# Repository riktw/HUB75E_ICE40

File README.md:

# HUB75E_ICE40
SpinalHDL code to drive a 64*64 pixel HUB75E module with an ICE40

This code is used to drive a HUB75E dislay, fast enough to display animated gifs:

This project uses SpinalHDL, see installation notes here: https://spinalhdl.github.io/SpinalDoc-RTD/SpinalHDL/Getting%20Started/index.html

To build, yosys and nextpnr are used, see installation notes here: http://www.clifford.at/icestorm/

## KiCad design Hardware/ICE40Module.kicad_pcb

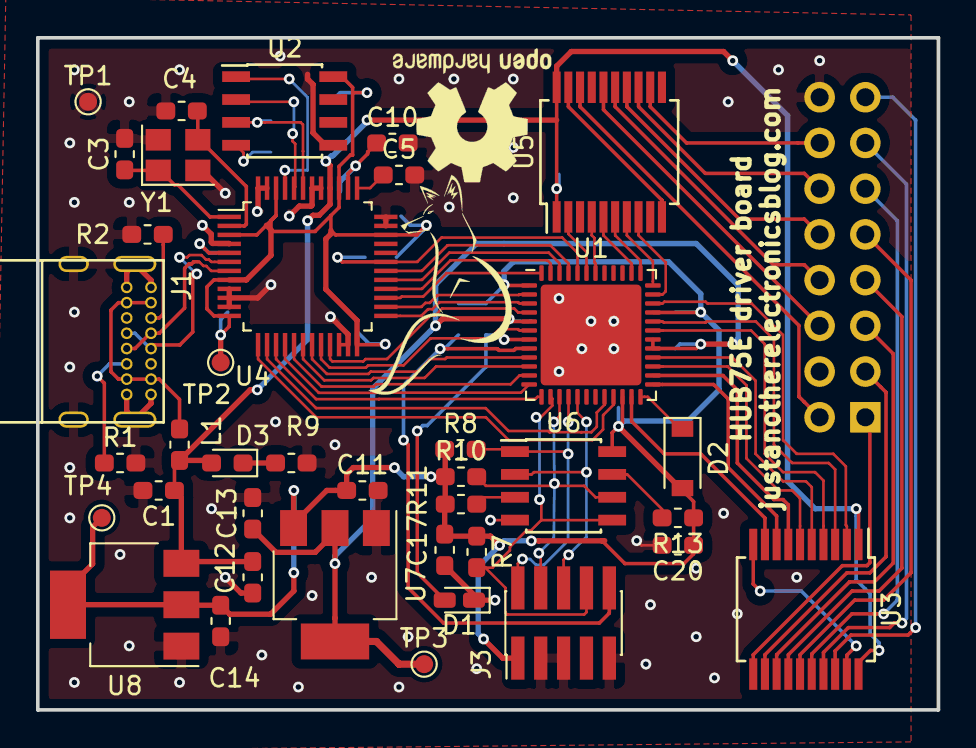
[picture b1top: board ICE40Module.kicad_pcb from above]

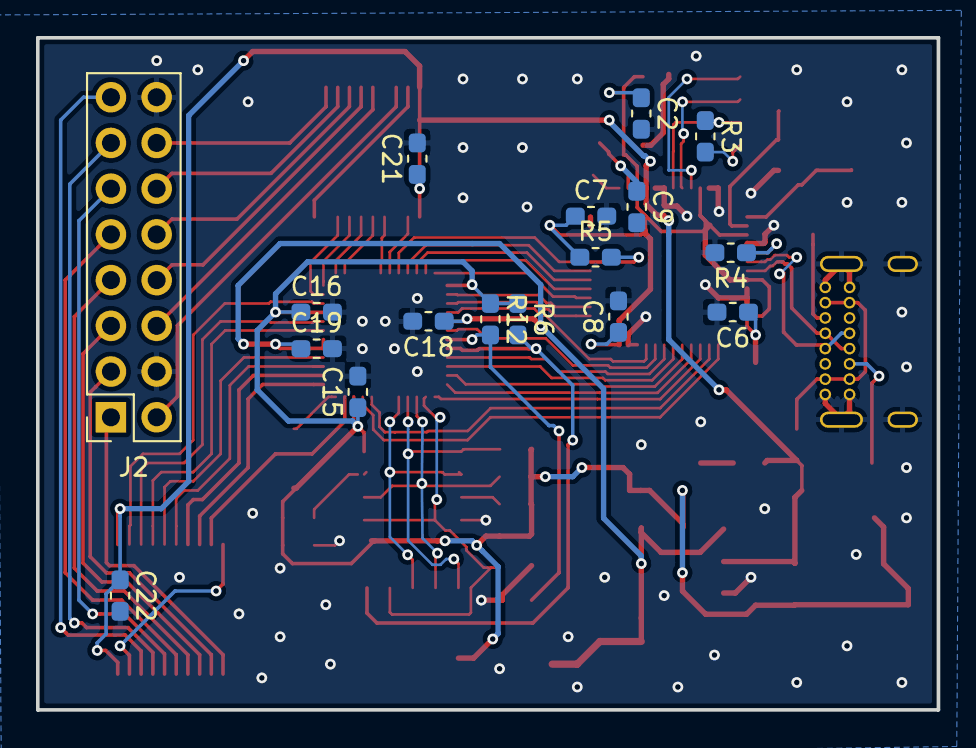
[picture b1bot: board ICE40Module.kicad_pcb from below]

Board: 2 copper layers, 50.0 x 37.3 mm, 55 parts (17 on the bottom side), 75 nets.

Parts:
C1, C8, C10, C18: 1u; C_0603_1608Metric_Pad1.05x0.95mm_HandSolder
C2, C5, C6, C7, C9, C11, C12, C13, C14, C15, C16, C17, C19, C20, C21, C22: 100n; C_0603_1608Metric_Pad1.05x0.95mm_HandSolder
C3, C4: 18p; C_0603_1608Metric_Pad1.05x0.95mm_HandSolder
D1: LED; LED_0603_1608Metric_Castellated
D2: MBR0520; D_SOD-123
D3: LED; LED_0603_1608Metric_Pad1.05x0.95mm_HandSolder
J1: USB_C_Recept_16Pin
J2: Conn_02x08_Odd_Even; PinSocket_2x08_P2.54mm_Vertical
J3: Conn_ARM_JTAG_SWD_10; PinHeader_2x05_P1.27mm_Vertical_SMD
L1: 22R; L_0603_1608Metric_Pad1.05x0.95mm_HandSolder
R1, R2, R5: 5.1K; R_0603_1608Metric_Pad1.05x0.95mm_HandSolder
R3, R12: 2.2K; R_0603_1608Metric_Pad1.05x0.95mm_HandSolder
R4: 12K; R_0603_1608Metric_Pad1.05x0.95mm_HandSolder
R6, R7, R8, R10, R11, R13: 10K; R_0603_1608Metric_Pad1.05x0.95mm_HandSolder
R9: 680R; R_0603_1608Metric_Pad1.05x0.95mm_HandSolder
TP1, TP2, TP3, TP4: TP; TestPoint_Pad_D1.0mm
U1: ICE40UP5K-SG48ITR; QFN-48-1EP_7x7mm_P0.5mm_EP5.6x5.6mm
U2: 93LCxxB; SOIC-8_3.9x4.9mm_P1.27mm
U3, U5: 74HC245; SSOP-20_5.3x7.2mm_P0.65mm
U4: FT232H; LQFP-48_7x7mm_P0.5mm
U6: AT25SF081-SSHD-X; SOIC-8_3.9x4.9mm_P1.27mm
U7: AZ1117-1.2; SOT-223-3_TabPin2
U8: AP1117-33; SOT-223-3_TabPin2
Y1: 12Mhz; Crystal_SMD_3225-4Pin_3.2x2.5mm

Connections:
+1V2: C13.1, C18.1, C19.1, TP3.1, U1.5, U1.29, U1.30, U7.2
+1V8: C9.1, C10.1, U4.38
+3.3VA: C2.1, C6.1, C7.1, C8.1, R5.1, TP2.1, U2.8, U4.3, U4.8, U4.12, U4.24, U4.34, U4.39, U4.46
+3V3: C11.1, C14.1, C15.1, C16.1, C17.1, C20.1, D2.2, J3.1, R6.1, R7.1, R8.1, R10.1, R11.1, R12.1, R13.1, TP4.1, U1.1, U1.22, U1.33, U6.8, U7.3, U8.2
+5V: C1.1, C12.1, C21.1, C22.1, D3.2, L1.1, U3.1, U3.20, U4.40, U5.1, U5.20, U8.3
/USB_N: J1.A7, J1.B7, U4.6
/USB_P: J1.A6, J1.B6, U4.7
A0: U1.28, U3.5
A1: U1.37, U5.6
A2: U1.31, U3.4
A3: U1.36, U5.7
A4: U1.38, U5.5
B0: U1.25, U3.8
B1: U1.27, U3.6
BLANK: U1.34, U3.2
CS: J3.2, R8.2, U1.16, U6.1
D0: U1.21, U4.13
D1: U1.20, U4.14
D2: U1.13, U4.15
D3: U1.12, U4.16
D4: U1.11, U4.17
D5: U1.10, U4.18
D6: U1.9, U4.19
D7: U1.6, U4.20
D8: U1.4, U4.21
D9: U1.3, U4.25
D10: U1.2, U4.26
D11: U1.48, U4.27
D12: U1.47, U4.28
D13: U1.46, U4.29
D14: U1.45, U4.30
D15: R5.2, U1.44, U4.31
G0: U1.43, U5.2
G1: U1.42, U5.4
GND: C1.2, C2.2, C3.2, C4.2, C5.2, C6.2, C7.2, C8.2, C9.2, C10.2, C11.2, C12.2, C13.2, C14.2, C15.2, C16.2, C17.2, C18.2, C19.2, C20.2, C21.2, C22.2, D1.1, J1.A1, J1.A12, J1.B1, J1.B12, J1.S1, J2.4, J2.16, J3.3, J3.5, J3.9, R1.2, R2.2, R4.2, R9.1, TP1.1, U1.49, U2.5, U4.4, U4.9, U4.10, U4.11, U4.22, U4.23, U4.35, U4.36, U4.41, U4.42, U4.47, U4.48, U6.4, U7.1, U8.1, Y1.2, Y1.4
LATCH: U1.35, U5.8
unnamed: C3.1, U4.1, Y1.1
unnamed: C4.1, U4.2, Y1.3
unnamed: C5.1, U4.37
unnamed: D1.2, R12.2, U1.7
unnamed: D2.1, U1.24
unnamed: D3.1, R9.2
unnamed: J1.A4, J1.A9, J1.B4, J1.B9, L1.2
unnamed: J1.A5, R2.1
unnamed: J1.B5, R1.1
unnamed: J2.1, U3.11
unnamed: J2.2, U5.18
unnamed: J2.3, U3.12
unnamed: J2.5, U3.13
unnamed: J2.6, U5.16
unnamed: J2.7, U3.14
unnamed: J2.8, U5.15
unnamed: J2.9, U3.15
unnamed: J2.10, U5.14
unnamed: J2.11, U3.16
unnamed: J2.12, U5.13
unnamed: J2.13, U3.17
unnamed: J2.14, U5.12
unnamed: J2.15, U3.18
unnamed: R3.1, U2.3, U4.43
unnamed: R3.2, U2.4
unnamed: R4.1, U4.5
unnamed: R11.2, U6.3
unnamed: R13.2, U6.7
unnamed: U2.1, U4.45
unnamed: U2.2, U4.44
unnamed: U3.10, U3.19
unnamed: U5.10, U5.19
R0: U1.23, U3.9
R1: U1.26, U3.7
RST: J3.10, R6.2, U1.8
SCK: J3.4, R10.2, U1.15, U6.6
SCLK: U1.32, U3.3
SDI: J3.6, U1.17, U6.2
SDO: J3.8, R7.2, U1.14, U6.5

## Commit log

2020-04-26 Initial commit with code
2020-04-26 Derp, filename wrong
2020-05-09 Added hardware files
